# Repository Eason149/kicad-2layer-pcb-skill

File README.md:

# kicad-2layer-pcb

让 AI 智能体用 KiCad **从零新画普通双面板**的 Agent Skill：需求 → 原理图 → 布局 → 布线 → 铺铜 → 检查 → 交付 KiCad 工程。

> **状态：实验性。** 已在 KiCad 10.0.6（Windows）上从零画通一块小板（见[示例](#示例)）。SES 导入、较大的板子和 macOS/Linux 尚未验证。投产前必须由工程师复核。

## 能做什么

- 根据文字需求，或你提供的原理图，新建双面板工程
- 原理图必须真实可编辑，经你确认后锁定，之后不得改动
- 不添加 AI、工具、作者、日期、Logo、网址等水印（脚本拦截常见情况，仍需看图）
- ERC/DRC error、未连线、PCB 与原理图不一致、重叠未清零时，不放入 `output/`
- 额外查 KiCad DRC 不报的重叠：同网络走线、过孔在焊盘上、丝印与过孔等
- 只交付工程文件，不含日志、报告、渲染图、Gerber

**不适用**：4 层及以上、HDI、盲埋孔、受控阻抗、特殊高速板。市电/高压、射频、天线、单面铝基板，或缺少参数的大电流设计会先停下来问你。

## 依赖

| 软件 | 用途 |
|---|---|
| 支持 Skill、能执行命令的智能体（如 Claude Code） | 运行本 skill |
| [KiCad 10](https://www.kicad.org/download/) | 原理图、PCB、ERC/DRC |
| [Freerouting](https://github.com/freerouting/freerouting/releases) | 自动布线（小板可不用） |
| Java | 仅 Freerouting 需要，版本以其发布说明为准 |
| Python 3.9+ | 运行检查脚本，无第三方依赖 |

## 安装

先克隆仓库并进入目录：

```text
git clone https://github.com/Eason149/kicad-2layer-pcb-skill.git
cd kicad-2layer-pcb-skill
```

Windows（PowerShell）：

```powershell
New-Item -ItemType Directory -Force "$HOME\.claude\skills" | Out-Null; Copy-Item -Recurse -Force skills\kicad-2layer-pcb "$HOME\.claude\skills\"
```

macOS / Linux：

```bash
mkdir -p ~/.claude/skills && cp -R skills/kicad-2layer-pcb ~/.claude/skills/
```

只想在某个项目里用，就复制到该项目的 `.claude/skills/`。其他智能体请让它读取 `skills/kicad-2layer-pcb/SKILL.md`。

检查环境（在仓库目录，macOS/Linux 用 `python3`）：

```text
python skills/kicad-2layer-pcb/scripts/doctor.py
```

找不到软件时设置环境变量：`KICAD_CLI`、`KICAD_PYTHON`（KiCad 自带的 Python）、`FREEROUTING_JAR`。

## 使用

在智能体里直接说：

```text
用 kicad-2layer-pcb 画一块双面板：
12V 输入，5V/2A 输出，50×40 mm，四角 M3 安装孔，
接线端子输入，USB-A 输出。
```

流程：补问缺少的参数 → 画原理图并跑 ERC → **等你确认** → 锁定原理图 → 布局布线铺铜 → DRC 修错 → 交付。

```text
output/<工程名>/     通过全部检查的工程
未完成/<工程名>/     未通过的最好结果
```

## 示例

[examples/NE555_Flasher](examples/NE555_Flasher)：5V NE555 LED 闪烁板，40×30 mm，四角 M3 孔。ERC 和 DRC 0 错误 0 警告，未连线、一致性问题、重叠均为 0。

生成程序在 [examples/scripts](examples/scripts)，**专为这块板写**，其中的模拟退火布局和两层 A* 布线可作参考。不含 Freerouting。

已知不足：安装孔没有预留螺钉头禁铜区，布局还有优化空间，没有打样验证。

## 目录

```text
skills/kicad-2layer-pcb/
  SKILL.md                    流程与规则
  scripts/doctor.py           环境检查
  scripts/check_project.py    锁定原理图、检查、交付
  scripts/check_overlap.py    重叠检查（用 KiCad 自带 Python）
  scripts/kicad_adapter.py    DSN 导出、SES 导入、铺铜（用 KiCad 自带 Python）
  assets/sheet.kicad_wks      无水印图框
examples/                     示例工程与生成程序
```

## 已知限制

- 没有通用的布局、建板、布线程序，由智能体参考示例为每块板编写
- 丝印出板框、被器件遮挡、过孔互相重叠这几项检查未做反向测试
- 水印检查基于关键词和图片，可能漏判或误判
- DRC 通过不代表载流、散热、EMC、安规合格

## 许可证

[MIT](LICENSE)。KiCad、Freerouting 等第三方软件遵循各自的许可证。

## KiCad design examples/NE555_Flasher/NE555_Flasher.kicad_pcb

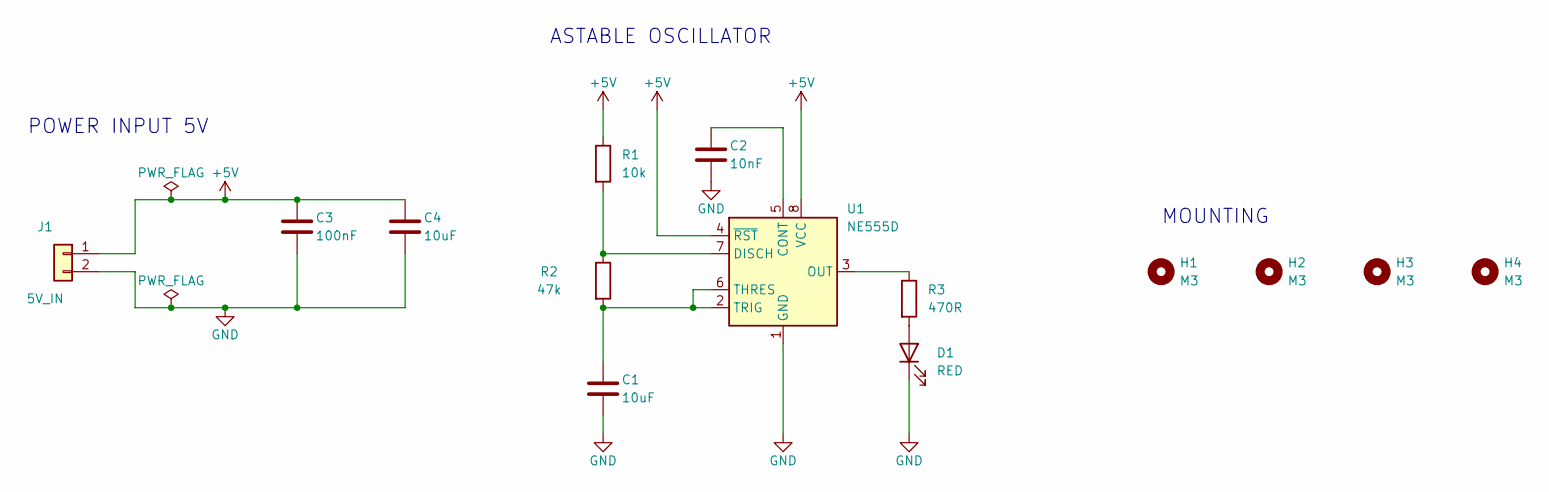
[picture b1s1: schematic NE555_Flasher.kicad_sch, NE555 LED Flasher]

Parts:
C1, C4: 10uF; C_0805_2012Metric
C2: 10nF; C_0805_2012Metric
C3: 100nF; C_0805_2012Metric
D1: RED; LED_0805_2012Metric
H1, H2, H3, H4: M3; MountingHole_3.2mm_M3
J1: 5V_IN; PinHeader_1x02_P2.54mm_Vertical
R1: 10k; R_0805_2012Metric
R2: 47k; R_0805_2012Metric
R3: 470R; R_0805_2012Metric
U1: NE555D; SOIC-8_3.9x4.9mm_P1.27mm

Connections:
+5V: C3.1, C4.1, J1.1, R1.1, U1.4 (~RST), U1.8 (VCC)
GND: C1.2, C2.2, C3.2, C4.2, D1.1 (K), J1.2, U1.1 (GND)
unnamed: D1.2 (A), R3.2
unnamed: C2.1, U1.5 (CONT)
unnamed: R1.2, R2.1, U1.7 (DISCH)
unnamed: R3.1, U1.3 (OUT)
unnamed: C1.1, R2.2, U1.2 (TRIG), U1.6 (THRES)

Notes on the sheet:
POWER INPUT 5V
ASTABLE OSCILLATOR
MOUNTING

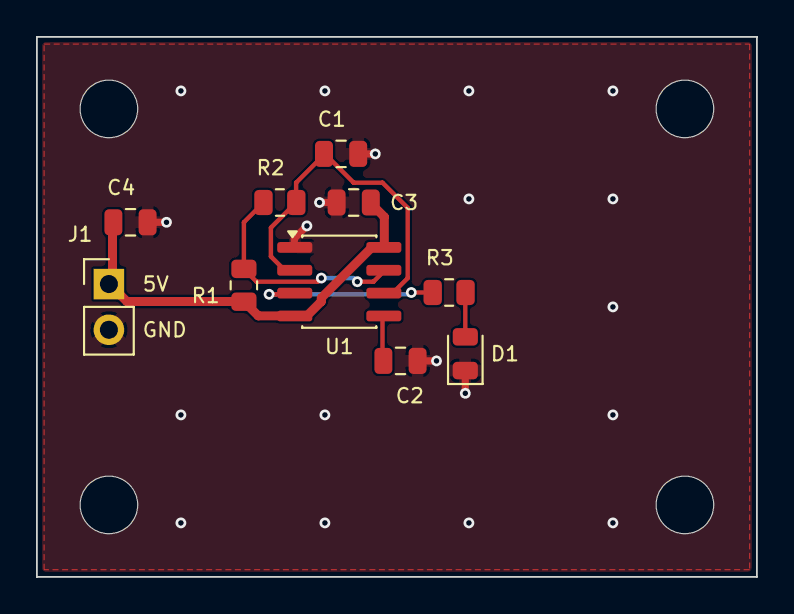
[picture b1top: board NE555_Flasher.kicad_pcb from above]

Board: 2 copper layers, 40.0 x 30.0 mm, 14 parts (0 on the bottom side), 7 nets.
